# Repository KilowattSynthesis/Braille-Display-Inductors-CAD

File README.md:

# Braille-Display-Inductors-CAD

Braille display POC using SMD inductors as solenoids (Type 3)

## Braille Display Type 3 - Using SMD Inductors as Solenoids

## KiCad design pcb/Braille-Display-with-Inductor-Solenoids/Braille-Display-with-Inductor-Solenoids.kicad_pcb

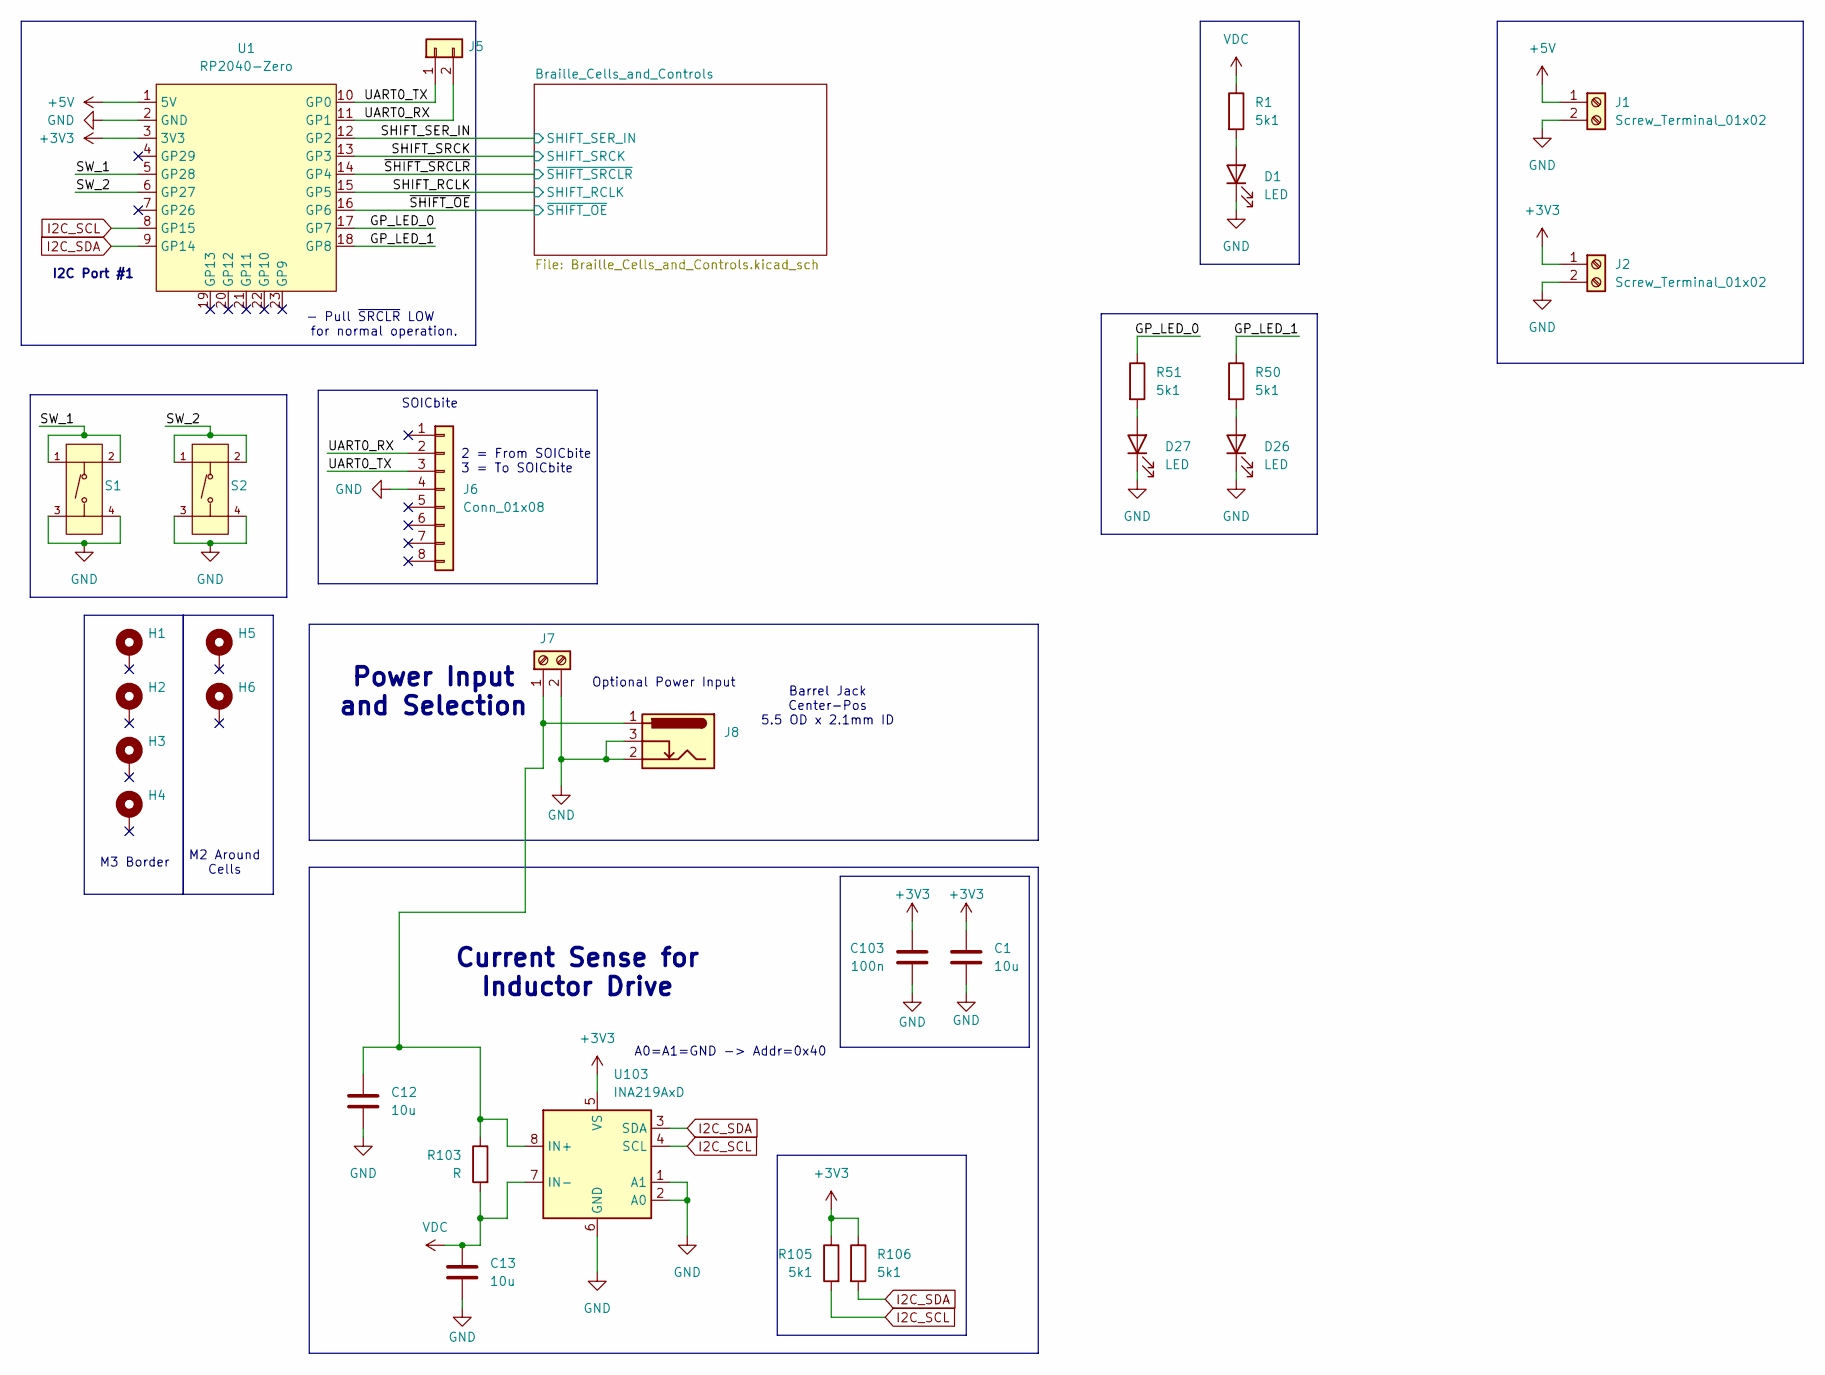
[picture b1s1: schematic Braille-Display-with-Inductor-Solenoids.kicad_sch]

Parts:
C1, C12, C13: 10u; C_1206_3216Metric_Pad1.33x1.80mm_HandSolder
C103: 100n; C_0603_1608Metric_Pad1.08x0.95mm_HandSolder
D1, D26, D27: LED; LED_0603_1608Metric_Pad1.05x0.95mm_HandSolder
H1, H2, H3, H4: MountingHole_Pad; MountingHole_3.2mm_M3_Pad
H5, H6: MountingHole_Pad; Braille_Block_MountingHoles_M2_3x
J1, J2, J7: Screw_Terminal_01x02; TerminalBlock_bornier-2_P5.08mm
J5: Conn_01x02; PinHeader_1x02_P2.54mm_Vertical
J6: Conn_01x08; SOICbite_clipProgSmall
J8: Barrel_Jack_Switch; BarrelJack_Horizontal
R1, R50, R51, R105, R106: 5k1; R_0603_1608Metric_Pad0.98x0.95mm_HandSolder
R103: R; R_1206_3216Metric_Pad1.30x1.75mm_HandSolder
S1, S2: Tactile Button, 160gf; SW-SMD_4P-L5.1-W5.1-P3.70-LS6.5-TL-2; Voltage Rating (Dc) 12V; Part TS-1187A-B-A-B; LCSC C318884
U1: RP2040-Zero; RP2040 Zero
U103: INA219AxD; SOIC-8_3.9x4.9mm_P1.27mm

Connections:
+3V3: C1.1, C103.1, J2.1, R105.1, R106.1, U1.3 (3V3), U103.5 (VS); also elsewhere on the board
+5V: J1.1, U1.1 (5V)
/GP_LED_0: R51.1, U1.17 (GP7)
/GP_LED_1: R50.1, U1.18 (GP8)
/SHIFT_RCLK: U1.15 (GP5); also elsewhere on the board
/SHIFT_SER_IN: U1.12 (GP2); also elsewhere on the board
/SHIFT_SRCK: U1.13 (GP3); also elsewhere on the board
/SW_1: S1.1 (A), S1.2 (B), U1.5 (GP28)
/SW_2: S2.1 (A), S2.2 (B), U1.6 (GP27)
/UART0_RX: J5.2, J6.2, U1.11 (GP1)
/UART0_TX: J5.1, J6.3, U1.10 (GP0)
/~SHIFT_OE: U1.16 (GP6); also elsewhere on the board
/~SHIFT_SRCLR: U1.14 (GP4); also elsewhere on the board
GND: C1.2, C12.2, C13.2, C103.2, D1.1 (K), D26.1 (K), D27.1 (K), J1.2, J2.2, J6.4, J7.2, J8.2, J8.3, S1.3 (C), S1.4 (D), S2.3 (C), S2.4 (D), U1.2 (GND), U103.1 (A1), U103.2 (A0), U103.6 (GND); also elsewhere on the board
I2C_SCL: R105.2, U1.8 (GP15), U103.4 (SCL)
I2C_SDA: R106.2, U1.9 (GP14), U103.3 (SDA)
unnamed: D1.2 (A), R1.2
unnamed: D26.2 (A), R50.2
unnamed: D27.2 (A), R51.2
unnamed: C12.1, J7.1, J8.1, R103.1, U103.8 (IN+)
VDC: C13.1, R1.1, R103.2, U103.7 (IN-); also elsewhere on the board

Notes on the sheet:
Barrel Jack Center-Pos 5.5 OD x 2.1mm ID
I2C Port #1
SOICbite
2 = From SOICbite 3 = To SOICbite
Optional Power Input
M2 Around Cells
- Pull ~{SRCLR} LOW for normal operation.
M3 Border
A0=A1=GND -> Addr=0x40
Power Input and Selection
Current Sense for Inductor Drive

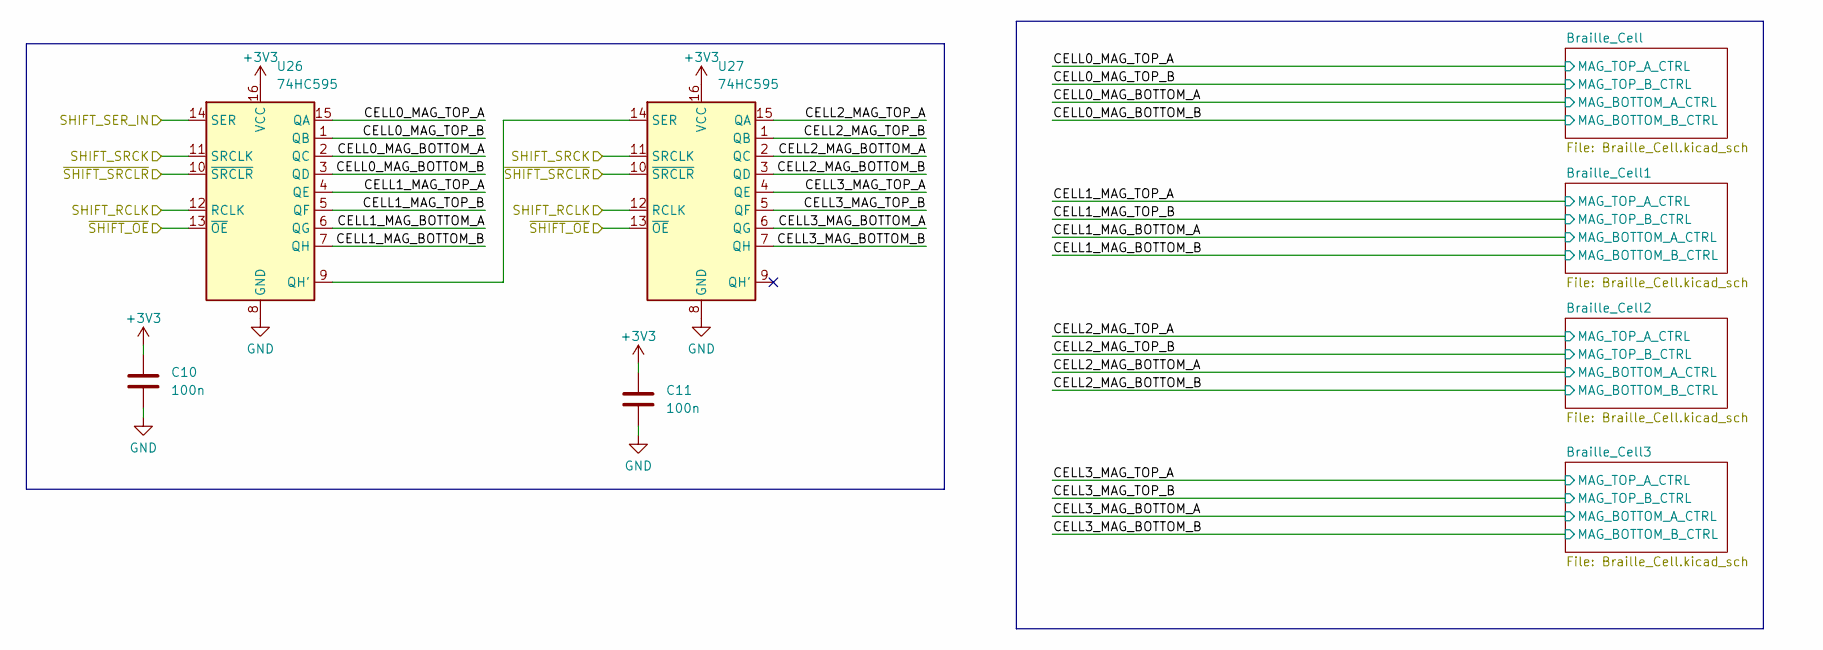
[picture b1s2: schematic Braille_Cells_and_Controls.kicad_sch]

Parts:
C10, C11: 100n; C_0603_1608Metric_Pad1.08x0.95mm_HandSolder
U26, U27: 74HC595; SOP-16_3.9x9.9mm_P1.27mm

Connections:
+3V3: C10.1, C11.1, U26.16 (VCC), U27.16 (VCC); also elsewhere on the board
/Braille_Cells_and_Controls/CELL0_MAG_BOTTOM_A: U26.2 (QC); also elsewhere on the board
/Braille_Cells_and_Controls/CELL0_MAG_BOTTOM_B: U26.3 (QD); also elsewhere on the board
/Braille_Cells_and_Controls/CELL0_MAG_TOP_A: U26.15 (QA); also elsewhere on the board
/Braille_Cells_and_Controls/CELL0_MAG_TOP_B: U26.1 (QB); also elsewhere on the board
/Braille_Cells_and_Controls/CELL1_MAG_BOTTOM_A: U26.6 (QG); also elsewhere on the board
/Braille_Cells_and_Controls/CELL1_MAG_BOTTOM_B: U26.7 (QH); also elsewhere on the board
/Braille_Cells_and_Controls/CELL1_MAG_TOP_A: U26.4 (QE); also elsewhere on the board
/Braille_Cells_and_Controls/CELL1_MAG_TOP_B: U26.5 (QF); also elsewhere on the board
/Braille_Cells_and_Controls/CELL2_MAG_BOTTOM_A: U27.2 (QC); also elsewhere on the board
/Braille_Cells_and_Controls/CELL2_MAG_BOTTOM_B: U27.3 (QD); also elsewhere on the board
/Braille_Cells_and_Controls/CELL2_MAG_TOP_A: U27.15 (QA); also elsewhere on the board
/Braille_Cells_and_Controls/CELL2_MAG_TOP_B: U27.1 (QB); also elsewhere on the board
/Braille_Cells_and_Controls/CELL3_MAG_BOTTOM_A: U27.6 (QG); also elsewhere on the board
/Braille_Cells_and_Controls/CELL3_MAG_BOTTOM_B: U27.7 (QH); also elsewhere on the board
/Braille_Cells_and_Controls/CELL3_MAG_TOP_A: U27.4 (QE); also elsewhere on the board
/Braille_Cells_and_Controls/CELL3_MAG_TOP_B: U27.5 (QF); also elsewhere on the board
/SHIFT_RCLK: U26.12 (RCLK), U27.12 (RCLK); also elsewhere on the board
/SHIFT_SER_IN: U26.14 (SER); also elsewhere on the board
/SHIFT_SRCK: U26.11 (SRCLK), U27.11 (SRCLK); also elsewhere on the board
/~SHIFT_OE: U26.13 (~OE), U27.13 (~OE); also elsewhere on the board
/~SHIFT_SRCLR: U26.10 (~SRCLR), U27.10 (~SRCLR); also elsewhere on the board
GND: C10.2, C11.2, U26.8 (GND), U27.8 (GND); also elsewhere on the board
unnamed: U26.9 (QH'), U27.14 (SER)

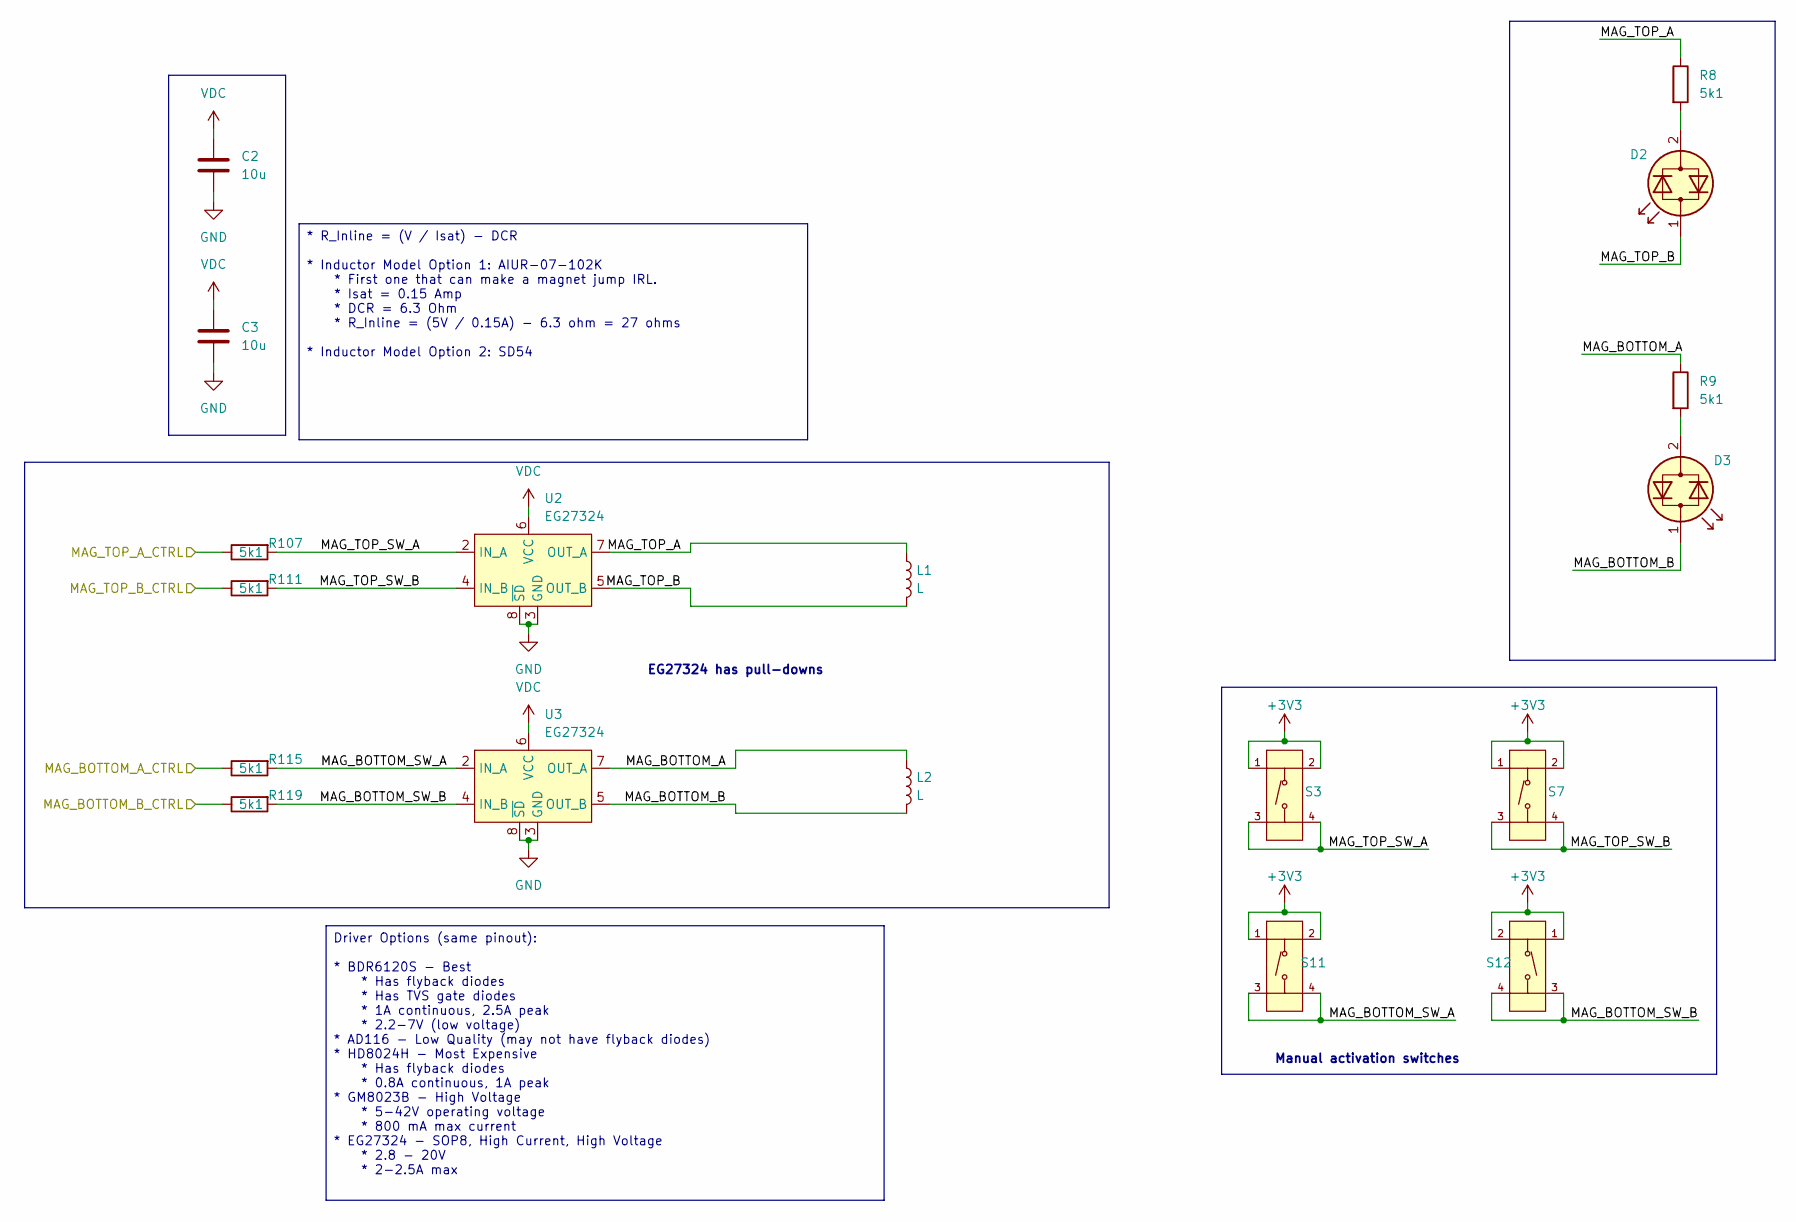
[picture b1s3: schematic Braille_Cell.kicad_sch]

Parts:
C2, C3: 10u; C_1206_3216Metric_Pad1.33x1.80mm_HandSolder
D2, D3: LED_Dual_Bidirectional; LED_0603_1608Metric_HandSolder_2x_Reverse
L1, L2: L; Inductor_6mm_AIUR-07-102K_THT_SD54_SMD
R8, R9, R107, R111, R115, R119: 5k1; R_0603_1608Metric_Pad0.98x0.95mm_HandSolder
S3, S7, S11, S12: Tactile Button, 160gf; SW-SMD_4P-L5.1-W5.1-P3.70-LS6.5-TL-2; Voltage Rating (Dc) 12V; Part TS-1187A-B-A-B; LCSC C318884
U2, U3: EG27324; SOP-8_3.9x4.9mm_P1.27mm

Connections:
+3V3: S3.1 (A), S3.2 (B), S7.1 (A), S7.2 (B), S11.1 (A), S11.2 (B), S12.1 (A), S12.2 (B); also elsewhere on the board
/Braille_Cells_and_Controls/Braille_Cell/MAG_BOTTOM_A: L2.1, R9.1, U3.7 (OUT_A)
/Braille_Cells_and_Controls/Braille_Cell/MAG_BOTTOM_B: D3.1 (KA), L2.2, U3.5 (OUT_B)
/Braille_Cells_and_Controls/Braille_Cell/MAG_BOTTOM_SW_A: R115.2, S11.3 (C), S11.4 (D), U3.2 (IN_A)
/Braille_Cells_and_Controls/Braille_Cell/MAG_BOTTOM_SW_B: R119.2, S12.3 (C), S12.4 (D), U3.4 (IN_B)
/Braille_Cells_and_Controls/Braille_Cell/MAG_TOP_A: L1.1, R8.1, U2.7 (OUT_A)
/Braille_Cells_and_Controls/Braille_Cell/MAG_TOP_B: D2.1 (KA), L1.2, U2.5 (OUT_B)
/Braille_Cells_and_Controls/Braille_Cell/MAG_TOP_SW_A: R107.2, S3.3 (C), S3.4 (D), U2.2 (IN_A)
/Braille_Cells_and_Controls/Braille_Cell/MAG_TOP_SW_B: R111.2, S7.3 (C), S7.4 (D), U2.4 (IN_B)
/Braille_Cells_and_Controls/CELL0_MAG_BOTTOM_A: R115.1; also elsewhere on the board
/Braille_Cells_and_Controls/CELL0_MAG_BOTTOM_B: R119.1; also elsewhere on the board
/Braille_Cells_and_Controls/CELL0_MAG_TOP_A: R107.1; also elsewhere on the board
/Braille_Cells_and_Controls/CELL0_MAG_TOP_B: R111.1; also elsewhere on the board
GND: C2.2, C3.2, U2.3 (GND), U2.8 (~SD), U3.3 (GND), U3.8 (~SD); also elsewhere on the board
unnamed: D2.2 (AK), R8.2
unnamed: D3.2 (AK), R9.2
VDC: C2.1, C3.1, U2.6 (VCC), U3.6 (VCC); also elsewhere on the board

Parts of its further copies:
C4, C5, C6, C7, C8, C9: 10u; C_1206_3216Metric_Pad1.33x1.80mm_HandSolder
D4, D5, D6, D7, D8, D9: LED_Dual_Bidirectional; LED_0603_1608Metric_HandSolder_2x_Reverse
L3, L4, L5, L6, L7, L8: L; Inductor_6mm_AIUR-07-102K_THT_SD54_SMD
R6, R7, R12, R13, R16, R17, R108, R109, R110, R112, R113, R114, R116, R117, R118, R120, R121, R122: 5k1; R_0603_1608Metric_Pad0.98x0.95mm_HandSolder
S4, S5, S6, S8, S9, S10, S13, S14, S15, S16, S17, S18: Tactile Button, 160gf; SW-SMD_4P-L5.1-W5.1-P3.70-LS6.5-TL-2; Voltage Rating (Dc) 12V; Part TS-1187A-B-A-B; LCSC C318884
U4, U5, U6, U7, U8, U9: EG27324; SOP-8_3.9x4.9mm_P1.27mm

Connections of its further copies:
+3V3: S4.1 (A), S4.2 (B), S5.1 (A), S5.2 (B), S6.1 (A), S6.2 (B), S8.1 (A), S8.2 (B), S9.1 (A), S9.2 (B), S10.1 (A), S10.2 (B), S13.1 (A), S13.2 (B), S14.1 (A), S14.2 (B), S15.1 (A), S15.2 (B), S16.1 (A), S16.2 (B), S17.1 (A), S17.2 (B), S18.1 (A), S18.2 (B); also elsewhere on the board
/Braille_Cells_and_Controls/Braille_Cell1/MAG_BOTTOM_A: L4.1, R7.1, U5.7 (OUT_A)
/Braille_Cells_and_Controls/Braille_Cell1/MAG_BOTTOM_B: D5.1 (KA), L4.2, U5.5 (OUT_B)
/Braille_Cells_and_Controls/Braille_Cell1/MAG_BOTTOM_SW_A: R116.2, S13.3 (C), S13.4 (D), U5.2 (IN_A)
/Braille_Cells_and_Controls/Braille_Cell1/MAG_BOTTOM_SW_B: R120.2, S14.3 (C), S14.4 (D), U5.4 (IN_B)
/Braille_Cells_and_Controls/Braille_Cell1/MAG_TOP_A: L3.1, R6.1, U4.7 (OUT_A)
/Braille_Cells_and_Controls/Braille_Cell1/MAG_TOP_B: D4.1 (KA), L3.2, U4.5 (OUT_B)
/Braille_Cells_and_Controls/Braille_Cell1/MAG_TOP_SW_A: R108.2, S4.3 (C), S4.4 (D), U4.2 (IN_A)
/Braille_Cells_and_Controls/Braille_Cell1/MAG_TOP_SW_B: R112.2, S8.3 (C), S8.4 (D), U4.4 (IN_B)
/Braille_Cells_and_Controls/Braille_Cell2/MAG_BOTTOM_A: L6.1, R13.1, U7.7 (OUT_A)
/Braille_Cells_and_Controls/Braille_Cell2/MAG_BOTTOM_B: D7.1 (KA), L6.2, U7.5 (OUT_B)
/Braille_Cells_and_Controls/Braille_Cell2/MAG_BOTTOM_SW_A: R117.2, S15.3 (C), S15.4 (D), U7.2 (IN_A)
/Braille_Cells_and_Controls/Braille_Cell2/MAG_BOTTOM_SW_B: R121.2, S16.3 (C), S16.4 (D), U7.4 (IN_B)
/Braille_Cells_and_Controls/Braille_Cell2/MAG_TOP_A: L5.1, R12.1, U6.7 (OUT_A)
/Braille_Cells_and_Controls/Braille_Cell2/MAG_TOP_B: D6.1 (KA), L5.2, U6.5 (OUT_B)
/Braille_Cells_and_Controls/Braille_Cell2/MAG_TOP_SW_A: R109.2, S5.3 (C), S5.4 (D), U6.2 (IN_A)
/Braille_Cells_and_Controls/Braille_Cell2/MAG_TOP_SW_B: R113.2, S9.3 (C), S9.4 (D), U6.4 (IN_B)
/Braille_Cells_and_Controls/Braille_Cell3/MAG_BOTTOM_A: L8.1, R17.1, U9.7 (OUT_A)
/Braille_Cells_and_Controls/Braille_Cell3/MAG_BOTTOM_B: D9.1 (KA), L8.2, U9.5 (OUT_B)
/Braille_Cells_and_Controls/Braille_Cell3/MAG_BOTTOM_SW_A: R118.2, S17.3 (C), S17.4 (D), U9.2 (IN_A)
/Braille_Cells_and_Controls/Braille_Cell3/MAG_BOTTOM_SW_B: R122.2, S18.3 (C), S18.4 (D), U9.4 (IN_B)
/Braille_Cells_and_Controls/Braille_Cell3/MAG_TOP_A: L7.1, R16.1, U8.7 (OUT_A)
/Braille_Cells_and_Controls/Braille_Cell3/MAG_TOP_B: D8.1 (KA), L7.2, U8.5 (OUT_B)
/Braille_Cells_and_Controls/Braille_Cell3/MAG_TOP_SW_A: R110.2, S6.3 (C), S6.4 (D), U8.2 (IN_A)
/Braille_Cells_and_Controls/Braille_Cell3/MAG_TOP_SW_B: R114.2, S10.3 (C), S10.4 (D), U8.4 (IN_B)
/Braille_Cells_and_Controls/CELL1_MAG_BOTTOM_A: R116.1; also elsewhere on the board
/Braille_Cells_and_Controls/CELL1_MAG_BOTTOM_B: R120.1; also elsewhere on the board
/Braille_Cells_and_Controls/CELL1_MAG_TOP_A: R108.1; also elsewhere on the board
/Braille_Cells_and_Controls/CELL1_MAG_TOP_B: R112.1; also elsewhere on the board
/Braille_Cells_and_Controls/CELL2_MAG_BOTTOM_A: R117.1; also elsewhere on the board
/Braille_Cells_and_Controls/CELL2_MAG_BOTTOM_B: R121.1; also elsewhere on the board
/Braille_Cells_and_Controls/CELL2_MAG_TOP_A: R109.1; also elsewhere on the board
/Braille_Cells_and_Controls/CELL2_MAG_TOP_B: R113.1; also elsewhere on the board
/Braille_Cells_and_Controls/CELL3_MAG_BOTTOM_A: R118.1; also elsewhere on the board
/Braille_Cells_and_Controls/CELL3_MAG_BOTTOM_B: R122.1; also elsewhere on the board
/Braille_Cells_and_Controls/CELL3_MAG_TOP_A: R110.1; also elsewhere on the board
/Braille_Cells_and_Controls/CELL3_MAG_TOP_B: R114.1; also elsewhere on the board
GND: C4.2, C5.2, C6.2, C7.2, C8.2, C9.2, U4.3 (GND), U4.8 (~SD), U5.3 (GND), U5.8 (~SD), U6.3 (GND), U6.8 (~SD), U7.3 (GND), U7.8 (~SD), U8.3 (GND), U8.8 (~SD), U9.3 (GND), U9.8 (~SD); also elsewhere on the board
unnamed: D4.2 (AK), R6.2
unnamed: D5.2 (AK), R7.2
unnamed: D6.2 (AK), R12.2
unnamed: D7.2 (AK), R13.2
unnamed: D8.2 (AK), R16.2
unnamed: D9.2 (AK), R17.2
VDC: C4.1, C5.1, C6.1, C7.1, C8.1, C9.1, U4.6 (VCC), U5.6 (VCC), U6.6 (VCC), U7.6 (VCC), U8.6 (VCC), U9.6 (VCC); also elsewhere on the board

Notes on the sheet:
Manual activation switches
EG27324 has pull-downs
Driver Options (same pinout): * BDR6120S - Best * Has flyback diodes * Has TVS gate diodes * 1A continuous, 2.5A peak * 2.2-7V (low voltage) * AD116 - Low Quality (may not have flyback diodes) * HD8024H - Most Expensive * Has flyback diodes * 0.8A continuous, 1A peak * GM8023B - High Voltage * 5-42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
* R_Inline = (V / Isat) - DCR * Inductor Model Option 1: AIUR-07-102K * First one that can make a magnet jump IRL. * Isat = 0.15 Amp * DCR = 6.3 Ohm * R_Inline = (5V / 0.15A) - 6.3 ohm = 27 ohms * Inductor Model Option 2: SD54

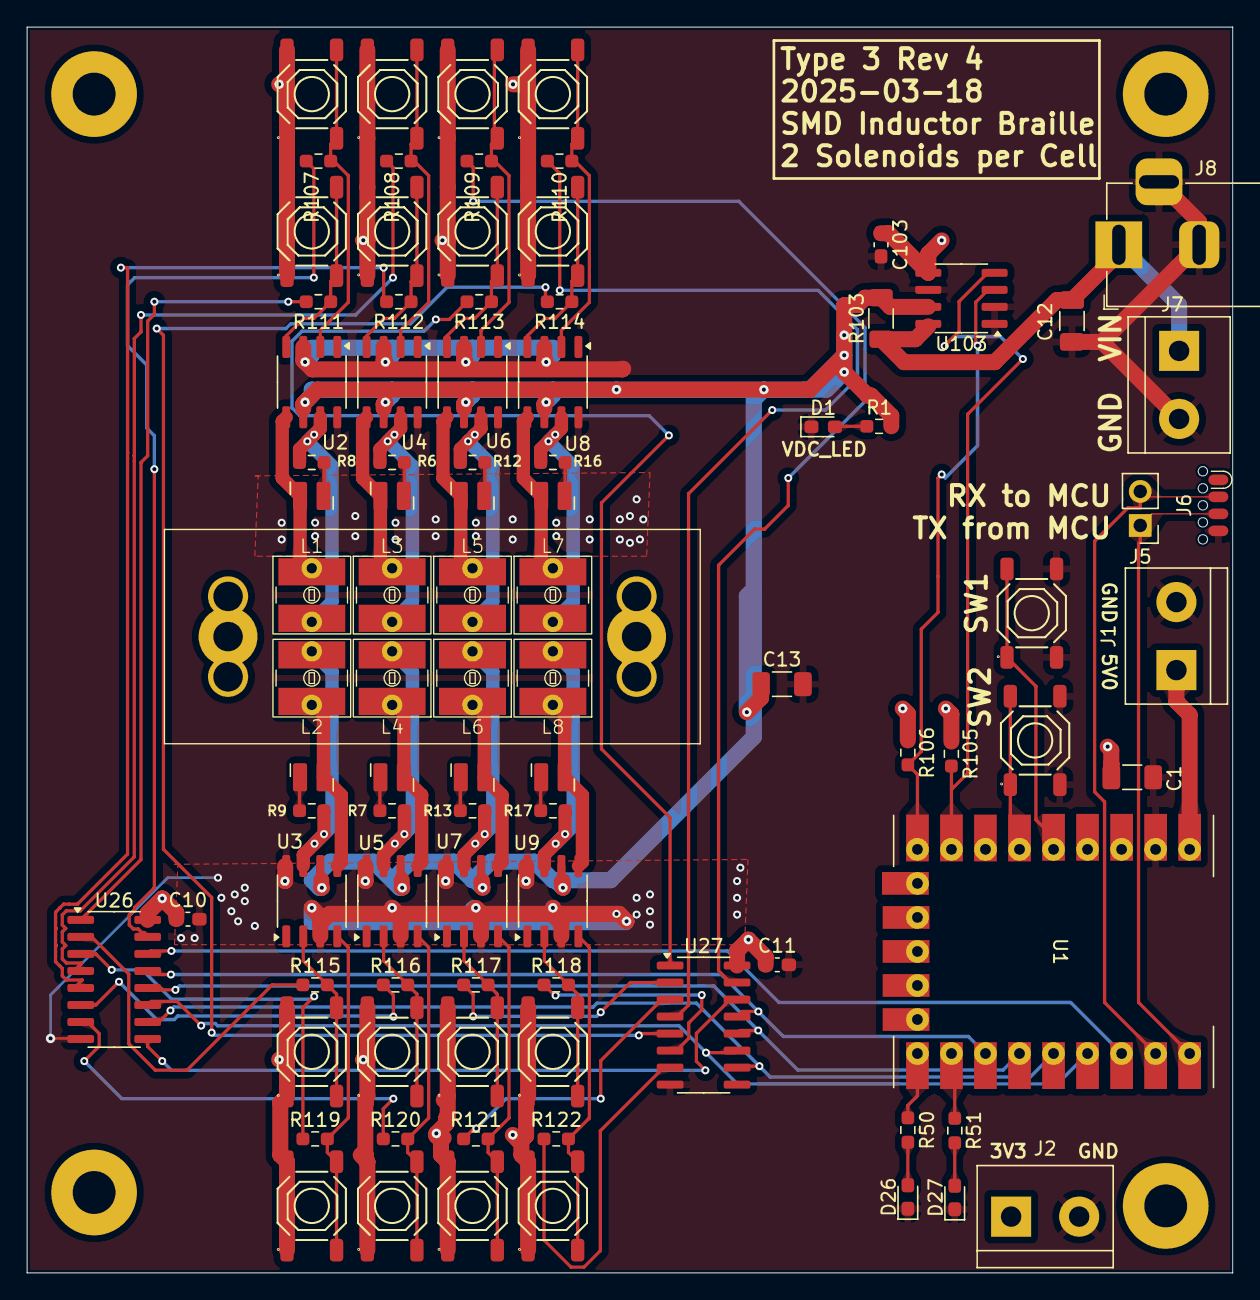
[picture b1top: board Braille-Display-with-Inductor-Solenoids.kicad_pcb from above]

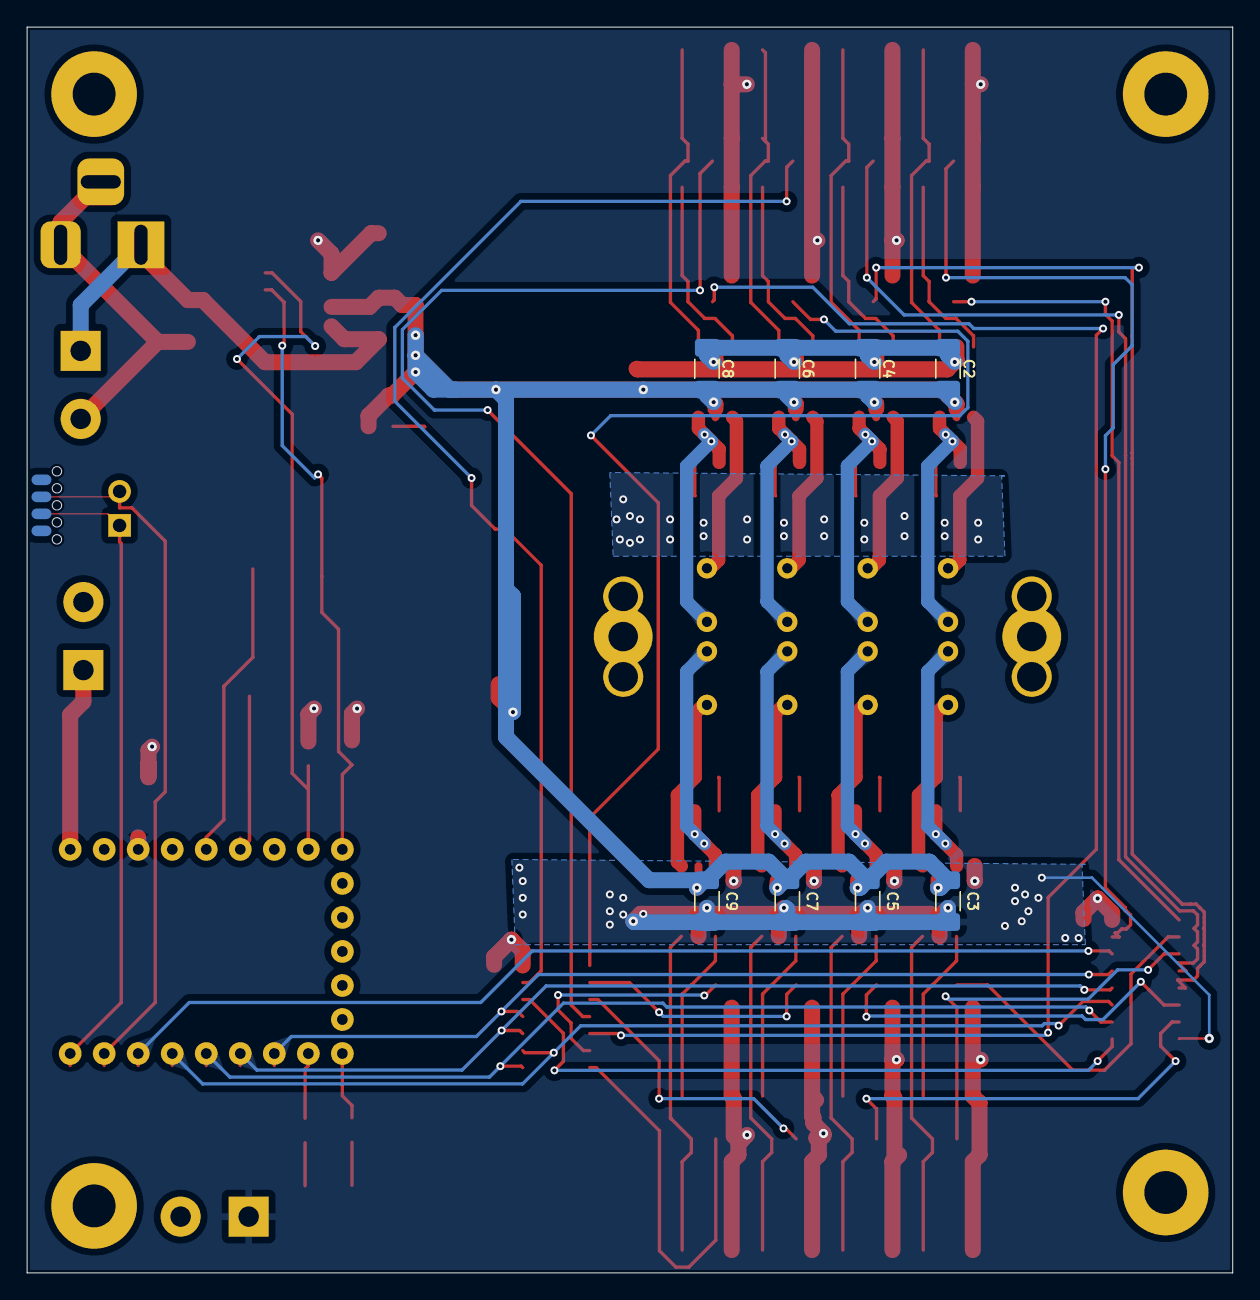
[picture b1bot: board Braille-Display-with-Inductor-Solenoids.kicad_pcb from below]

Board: 2 copper layers, 90.0 x 93.0 mm, 105 parts (8 on the bottom side), 78 nets.

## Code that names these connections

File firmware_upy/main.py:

from machine import Pin
import time

SHIFT_REGISTER_SLEEP_US = 10

# Pin definitions for shift register control
PIN_SHIFT_SER_IN = Pin(2, Pin.OUT)  # GP2: Serial data input
PIN_SHIFT_SRCK = Pin(3, Pin.OUT)  # GP3: Shift register clock
PIN_SHIFT_N_SRCLR = Pin(4, Pin.OUT)  # GP4: Shift register clear
PIN_SHIFT_RCLK = Pin(5, Pin.OUT)  # GP5: Register clock (latch)
PIN_SHIFT_N_OE = Pin(6, Pin.OUT)  # GP6: Output enable

PIN_SW1 = Pin(28, Pin.IN, Pin.PULL_UP)
PIN_SW2 = Pin(27, Pin.IN, Pin.PULL_UP)
PIN_GP_LED_0 = Pin(7, Pin.OUT)
PIN_GP_LED_1 = Pin(8, Pin.OUT)


def init_shift_register() -> None:
    """Initialize shift register pins to default states."""
    # Clear shift register.
    PIN_SHIFT_N_SRCLR.value(0)
    time.sleep_ms(SHIFT_REGISTER_SLEEP_US)
    PIN_SHIFT_N_SRCLR.value(1)  # Active low, so set to normal (not clearing).
    time.sleep_ms(SHIFT_REGISTER_SLEEP_US)

    PIN_SHIFT_N_OE.value(0)  # Active low, set low to enable outputs
    PIN_SHIFT_SRCK.value(0)  # Clock starts low
    PIN_SHIFT_RCLK.value(0)  # Latch starts low

    # Wait for initialization to complete
    time.sleep_ms(SHIFT_REGISTER_SLEEP_US)


def set_shift_registers(data: list[bool]) -> None:
    """
    Set the state of all shift registers based on input data.

    Args:
        data: list of 48 boolean values representing desired output states
             (6 registers x 8 bits per register)
    """
    if len(data) != 48:
        raise ValueError("Data must contain exactly 48 boolean values")

    # Shift out all 48 bits
    for bit in reversed(data):  # Shift MSB first
        # Set data bit.
        PIN_SHIFT_SER_IN.value(1 if bit else 0)
        time.sleep_us(SHIFT_REGISTER_SLEEP_US)

        # Clock in the bit.
        PIN_SHIFT_SRCK.value(1)
        time.sleep_us(SHIFT_REGISTER_SLEEP_US)
        PIN_SHIFT_SRCK.value(0)
        time.sleep_us(SHIFT_REGISTER_SLEEP_US)

    # Latch the data to outputs
    PIN_SHIFT_RCLK.value(1)
    time.sleep_us(SHIFT_REGISTER_SLEEP_US)
    PIN_SHIFT_RCLK.value(0)
    time.sleep_us(SHIFT_REGISTER_SLEEP_US)


def basic_demo() -> None:
    print("All outputs off (high-impedance)")
    outputs = [False] * 48  # All outputs off
    set_shift_registers(outputs)
    time.sleep(2)

    print("All outputs on - positive")
    outputs = [(i % 2 == 0) for i in range(48)]  # Alternating on/off pattern
    set_shift_registers(outputs)
    time.sleep(2)

    print("All outputs on - negative")
    outputs = [(i % 2 == 1) for i in range(48)]  # Alternating on/off pattern
    set_shift_registers(outputs)
    time.sleep(2)


def make_shift_register_state_single_dot(
    *, cell_number: int, dot_number: int, state: str
) -> list[bool]:
    """

    The AD116 is high-impedance when `IN_A = IN_B = 0`, and brake when `IN_A = IN_B = 1`.

    Args:
        cell_number: The cell number (0-3).
        dot_number: The dot number (1-6).
        state: Literal["brake", "high-z", "pos", "neg"]
    """

    # Initialize all dots to high-z.
    shift_register_state = [False] * 48

    # Map the state.
    in_a_in_b = {
        "brake": (True, True),
        "high-z": (False, False),
        "pos": (True, False),
        "neg": (False, True),
    }[state]

    # Set the state of the dot.
    base_offset = cell_number * 6 * 2 + (dot_number - 1) * 2
    shift_register_state[base_offset] = in_a_in_b[0]
    shift_register_state[base_offset + 1] = in_a_in_b[1]

    return shift_register_state


def make_shift_register_list_of_cells(
    cell_states: list[tuple[str, str, str, str, str, str] | str],
) -> list[bool]:
    """Convert a list of cell states to a list of shift register states."""
    shift_register_state = [False] * 48

    for cell_number, cell_state in enumerate(cell_states):
        if isinstance(cell_state, str):
            cell_state = (
                cell_state,
                cell_state,
                cell_state,
                cell_state,
                cell_state,
                cell_state,
            )

        for dot_number, state in enumerate(cell_state):
            base_offset = cell_number * 6 * 2 + dot_number * 2
            in_a_in_b = {
                "brake": (True, True),
                "high-z": (False, False),
                "pos": (True, False),
                "neg": (False, True),
            }[state]
            shift_register_state[base_offset] = in_a_in_b[0]
            shift_register_state[base_offset + 1] = in_a_in_b[1]

    return shift_register_state


def braille_demo() -> None:
    """Loop through each dot in each cells, and display it."""

    # for cell_number in range(4):
    # for dot_number in (1, 2, 3, 4, 5, 6):
    for cell_number in [1]:
        for dot_number in (4, 2, 6):
            # for state in ("brake", "high-z", "pos", "neg"):
            for state in ("brake", "pos", "neg"):
                print(f"Cell {cell_number}, Dot {dot_number}, State {state}")
                shift_register_state = make_shift_register_state_single_dot(
                    cell_number=cell_number, dot_number=dot_number, state=state
                )
                set_shift_registers(shift_register_state)
                time.sleep(1.5)


def braille_demo_try_to_roll_sphere() -> None:
    """Try to roll a sphere back and forth on a single cell."""
    for row_num in (0, 1, 2, 1):
        print(f"Row {row_num}")
        cell_state = [
            ("pos", "high-z", "high-z", "pos", "high-z", "high-z"),
            ("high-z", "pos", "high-z", "high-z", "pos", "high-z"),
            ("high-z", "high-z", "pos", "high-z", "high-z", "pos"),
        ][row_num]
        shift_register_state = make_shift_register_list_of_cells(
            [cell_state] + ["high-z"] * 3
        )

        set_shift_registers(shift_register_state)
        time.sleep(4)


def respond_to_buttons() -> None:
    """Respond to the button presses by setting the state of all.
    
    * Pressing SW1 sets all to "pos" for a short time, then back to high-z.
    * Pressing SW2 sets all to "neg" for a short time, then back to high-z.
    """

    ACTION_TIME_MS = 100
    DEBOUNCE_TIME_MS = 800

    if PIN_SW1.value() == 0:
        print("SW1 pressed.")
        PIN_GP_LED_0.value(1)
        direction = "pos"

    elif PIN_SW2.value() == 0:
        print("SW2 pressed.")
        PIN_GP_LED_1.value(1)
        direction = "neg"

    else:
        return

    set_shift_registers(make_shift_register_list_of_cells([direction] * 4))
    time.sleep_ms(ACTION_TIME_MS)
    set_shift_registers(make_shift_register_list_of_cells(["high-z"] * 4))
    print("Waiting for debounce.")
    time.sleep_ms(DEBOUNCE_TIME_MS)
    PIN_GP_LED_0.value(0)
    PIN_GP_LED_1.value(0)


def main() -> None:
    print("Starting init.")
    init_shift_register()
    PIN_GP_LED_0.value(0)
    PIN_GP_LED_1.value(0)
    print("Init complete.")

    while 0:
        print("Starting basic demo.")
        basic_demo()
        print("Basic demo complete.")

        print("Starting braille demo.")
        braille_demo()
        print("Braille demo complete.")

    while 1:
        respond_to_buttons()

    # while 1:
    #     print("Starting rolling sphere demo.")
    #     braille_demo_try_to_roll_sphere()


while True:
    main()

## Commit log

2024-11-17 Readd original project
2024-11-17 Remove symbol and footprint libraries
2024-11-17 Add top-type inductor footprint
2024-11-17 Add both inductors on same PCB, switch to new drivers
2024-11-17 Do layout
2024-11-17 Add breakouts, shrink SMD vertical inductor cutouts, add braille cell (4x now)
2024-11-17 Change page layout and reconnect components
2024-11-17 Layout debugging components
2024-11-17 Add UART soicbite
2024-11-17 Layout SOICbite footprint
2024-11-18 Clean up reference designator silkscreens, add layers
2024-11-18 Fix braille LED swap
2024-11-18 Finish routing and review
2024-11-18 Setup build123d CAD project
2024-11-27 Update SMD solenoid with THT pads
2024-11-27 Add holes to SMD inductors, prepare for Rev 2
2024-11-28 Start designing bottom housing, create CAD plan
2024-11-28 Create dot peg
2024-11-28 Add dot model and assembly
2024-11-28 Create the top-side housing
2024-11-28 Create stencil design
2024-11-28 Create printable 3d stencil
2024-11-28 Add solenoid protrusions, optimize bottom housing thickness
2024-11-30 Add top-to-bottom pegs
2024-11-30 Add stencil_2d exports, adjust sizing
2024-11-30 Make braille dot cluster for ordering
2024-11-30 PCB: Create Locking Stencil single instance
2024-11-30 Create stencil order
2024-11-30 Add specific sizing variations
2024-12-10 Switch to center through-hole and 2-way sliding for large solenoids
2024-12-11 Fix up X sizing and horizontal placement of stencil
2025-01-03 Create firmware for 48-dot shift registers
2025-01-03 Add Rev 2 FIXMEs
2025-01-03 Fix GitHub Actions with firmware in repo
2025-01-05 WIP (Rev3): Switch to 2 inductors per cell
2025-01-06 WIP: Route one cell
2025-01-06 WIP: Route more of the board
2025-01-06 WIP: Swap around power input placement
2025-01-06 Finish and polish design
2025-01-06 Bit of tiny routing, export production file
2025-01-06 PCB (Rev 3): Switch to 2 inductors per cell (#2)
    * WIP (Rev3): Switch to 2 inductors per cell
    * WIP: Route one cell
    * WIP: Route more of the board
    * WIP: Swap around power input placement
    * Finish and polish design
    * Bit of tiny routing, export production file
2025-01-06 Refactor CAD generation to support `dot_count_y=4`
2025-01-06 CAD: Simplify solenoid block removal, add dot drainage holes
2025-01-09 Add back-and-forth demo to firmware
2025-01-09 Update dot design for ordering
2025-01-10 Update firmware with button response actions (for rev-2 board)
2025-01-10 Update README explanation, label as Type 3
2025-01-10 Update README explanation, label as Type 3 (#3)
2025-03-13 pcb: Migrate to KiCAD v9
2025-03-18 pcb: WIP - Switch to new parts, layout
2025-03-18 pcb: WIP - High power and repeated routing
2025-03-18 Finish Rev 4
2025-03-18 Bump version numbers
